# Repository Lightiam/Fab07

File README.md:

# Fab07: ASIC GPU Fab Clean Readiness Package

This repository contains a complete, submission-ready fab clean package for building an ASIC GPU targeting the LightRail AI platform. The materials are organized following industry best practices for ASIC design and fabrication.

## Package Overview

This fab clean readiness package includes:

- **Architecture & Design Documentation** - Complete design specifications and microarchitecture
- **Physical Materials** - Silicon wafer, packaging, and board-level component specifications
- **Logical Materials** - IP blocks, RTL guidelines, and design architecture
- **Design Flow** - Complete toolchain and design methodology
- **Verification & Test** - Comprehensive verification strategy
- **NCE Reference Design** - Ready-to-adapt Neural Calibration Engine for LightRail AI

## Directory Structure

```
fab07/
├── README.md                          # This file
├── docs/                              # Design documentation
│   ├── ARCHITECTURE.md               # Overall system architecture
│   ├── MATERIALS_PHYSICAL.md         # Silicon, packaging, board specs
│   ├── MATERIALS_LOGICAL.md          # IP blocks and RTL guidelines
│   ├── DESIGN_FLOW.md                # Design methodology
│   └── COST_FEASIBILITY.md           # Cost and feasibility analysis
├── specs/                             # Detailed specifications
│   ├── silicon_spec.md               # Silicon wafer and process specs
│   ├── packaging_spec.md             # Package substrate specifications
│   ├── board_spec.md                 # Board-level materials and design
│   ├── thermal_spec.md               # Thermal and mechanical specs
│   └── ip_stack_spec.md              # IP core stack specifications
├── rtl/                               # RTL design and templates
│   ├── core/                         # GPU core modules
│   │   ├── simd_lane.sv              # SIMD execution lanes
│   │   ├── register_file.sv          # Register file architecture
│   │   └── cache_hierarchy.sv        # L0/L1/L2 cache implementation
│   ├── control/                      # Control plane modules
│   │   ├── command_processor.sv      # Host interface controller
│   │   ├── scheduler.sv              # Kernel and stream scheduler
│   │   └── dispatcher.sv             # Event-driven dispatcher
│   ├── memory/                       # Memory subsystem
│   │   ├── memory_controller.sv      # DDR/GDDR interface
│   │   └── l2_cache.sv               # L2/victim cache
│   ├── interfaces/                   # External interface IP
│   │   ├── pcie_controller.sv        # PCIe Gen4/5/6 PHY wrapper
│   │   └── memory_phy.sv             # DDR/LPDR/HBM PHY interface
│   ├── clock_power/                  # Clocking and power
│   │   ├── pll.sv                    # Phase-locked loops
│   │   └── power_gating.sv           # Power domain management
│   ├── test/                         # DFT and test
│   │   ├── scan_chain.sv             # Scan insertion framework
│   │   └── mbist_controller.sv       # SRAM MBIST
│   └── top/                          # Top-level design
│       └── gpu_asic_top.sv           # Top-level GPU module
├── verification/                     # Verification suite
│   ├── testbenches/                  # Unit and system testbenches
│   │   ├── lane_tb.sv                # SIMD lane testbench
│   │   ├── dispatcher_tb.sv          # Dispatcher testbench
│   │   └── system_tb.sv              # Full system testbench
│   ├── tests/                        # Test programs
│   │   ├── smoke_tests.sv            # Basic functionality tests
│   │   ├── regression_tests.sv       # Comprehensive regression suite
│   │   └── performance_tests.sv      # Performance validation
│   ├── uvm/                          # UVM verification framework
│   │   ├── env/                      # Verification environment
│   │   └── sequences/                # Test sequences
│   └── constraints/                  # Design constraints
│       ├── timing.sdc                # Timing constraints
│       └── power.tcl                 # Power constraints
├── tools/                            # Design flow tools and scripts
│   ├── synthesis/                    # Synthesis scripts
│   │   └── dc_synth.tcl              # Design Compiler flow
│   ├── pnr/                          # Place & Route flow
│   │   └── innovus_flow.tcl          # Innovus P&R script
│   ├── simulation/                   # Simulation infrastructure
│   │   ├── verilator_config.cpp      # Verilator configuration
│   │   └── vcs_waves.do              # Waveform capture setup
│   ├── lint/                         # Code quality checks
│   │   ├── verilint.cfg              # Verilint configuration
│   │   └── spyglass.waiver           # SpyGlass waiver file
│   └── dft/                          # DFT generation
│       ├── scan_def.txt              # Scan insertion definition
│       └── mbist_def.txt             # MBIST insertion definition
├── simulation/                       # Pre-built simulation models
│   ├── verilog/                      # RTL simulation models
│   └── spice/                        # SPICE extraction (as applicable)
├── implementation/                   # Physical implementation
│   ├── gds/                          # GDS-II layout files (after P&R)
│   ├── lef/                          # LEF macro definitions
│   ├── lib/                          # Liberty timing/power models
│   └── sdc/                          # Synopsys Design Constraints
├── nce_reference/                    # NCE (Neural Calibration Engine) Reference Design
│   ├── README.md                     # NCE design guide
│   ├── nce_core_top.sv               # Top-level NCE module
│   ├── components/                   # NCE component library
│   │   ├── simd_lane_nce.sv          # 128-lane SIMD datapath
│   │   ├── spiking_dispatcher.sv     # Event-triggered dispatcher
│   │   ├── neuron_block.sv           # 8-neuron calibration block
│   │   └── optical_output.sv         # Differential optical drivers
│   ├── validation/                   # NCE validation suite
│   │   ├── nce_smoke_test.sv         # Basic NCE test
│   │   └── nce_system_test.cpp       # Full NCE validation
│   └── lightrail_adaptation.md       # Guide to adapt NCE for LightRail AI
├── materials/                        # Bill of Materials and sourcing
│   ├── BOM.csv                       # Complete bill of materials
│   ├── SUPPLIERS.md                  # Supplier and vendor contacts
│   ├── IP_LICENSES.md                # IP licensing matrix
│   └── OPEN_SOURCE_STACK.md          # Open-source components used
├── reports/                          # Design reports and analyses
│   ├── ARCHITECTURE_REPORT.md        # Architecture analysis
│   ├── POWER_ANALYSIS.md             # Power estimation and breakdown
│   ├── TIMING_REPORT.md              # Timing closure analysis
│   ├── AREA_REPORT.md                # Area and resource utilization
│   └── COST_BREAKDOWN.md             # Cost analysis and ROI
├── checklists/                       # Pre-submission checklists
│   ├── PRE_SYNTHESIS.md              # Pre-synthesis checklist
│   ├── PRE_PNR.md                    # Pre-P&R checklist
│   ├── PRE_SIGNOFF.md                # Pre-signoff checklist
│   ├── FAB_SUBMISSION.md             # Fab submission checklist
│   └── DFT_VERIFICATION.md           # DFT verification checklist
└── standards/                        # Design standards and guidelines
    ├── CODING_STANDARDS.md           # Verilog coding standards
    ├── DESIGN_PATTERNS.md            # Reusable design patterns
    └── VERIFICATION_METHODOLOGY.md   # Verification methodology
```

## Key Artifacts

### 1. Physical Materials Stack
- **Silicon**: TSMC 28HPC/16FFC or GlobalFoundries 22FDX (mature nodes for cost-effective tapeout)
- **Packaging**: 2-3 layer organic laminate BGA substrate with signal/power planes
- **Board**: FR-4 high-speed PCB with 10-16 layers, optimized for PCIe + DDR4/GDDR6
- **Cooling**: Vapor chamber or copper heatsink with thermal interface materials

### 2. Logical Materials (IP Stack)
- **GPU Core**: 128-lane SIMD with vector ALUs, warp/wavefront scheduler
- **Memory Hierarchy**: L0/L1 per-lane caches, shared L2/L3 with victim buffers
- **On-chip Memory**: Shared memory/scratchpad for thread groups, register files
- **Control Plane**: Command processor, kernel scheduler, firmware management CPU
- **External Interfaces**: PCIe Gen4/5/6 PHY + controller, DDR4/GDDR6/HBM PHY
- **Clocking & Power**: PLL, clock gating, power domains, DVFS support

### 3. Design Flow (Complete Toolchain)
- **Front-end**: SystemVerilog/Verilog, simulation (Verilator/VCS/QuestaSim)
- **Synthesis**: Design Compiler or Genus for RTL-to-gate
- **Place & Route**: Innovus or OpenROAD for physical design
- **Verification**: UVM environment, formal verification, DRC/LVS closure
- **DFT**: Scan chains, MBIST for embedded SRAM, JTAG/boundary scan

### 4. Reference Design: NCE for LightRail AI
A 128-lane neuromorphic computation engine optimized for sparse spike-based ML inference:
- **Architecture**: Event-driven spiking dispatcher with watchdog-based clock gating
- **Datapath**: 128-lane SIMD with bfloat16 precision, vector registers
- **Calibration Block**: 8-neuron SPI-controlled neuron calibration with DAC/comparator interface
- **Optical I/O**: Modulated differential optical outputs for direct spike transmission
- **Memory**: Shared SRAM for synaptic weights, SPI-based external configuration

## Getting Started

### 1. Review Architecture
Start with `docs/ARCHITECTURE.md` for the overall system design and rationale.

### 2. Examine Specifications
Review the detailed specifications in `specs/` directory:
- Silicon and process technology choices
- Package substrate design
- PCB board specifications
- IP core stack and interface specifications

### 3. Explore RTL Design
The `rtl/` directory contains modular, synthesizable Verilog/SystemVerilog:
- Each core module is self-contained with clear I/O contracts
- Design follows GPU best practices from VeriGPU and OpenGPU
- Register file and memory interfaces use parametrized templates

### 4. Run Verification
See `verification/README.md` for:
- Simulation setup and execution
- Testbench architecture
- Coverage metrics and closure

### 5. Adapt NCE for LightRail
Follow `nce_reference/lightrail_adaptation.md` to customize the Neural Calibration Engine for your specific LightRail AI workloads.

## Dependencies and Open-Source Stack

This design builds on proven open-source components:

| Component | Source | Purpose |
|-----------|--------|---------|
| GPU Core RTL | VeriGPU | ML-focused RISC-V GPU architecture |
| Alt. GPU Ref | OpenGPU, MIAOW | Graphics pipeline, microarchitecture inspiration |
| ASIC Flow | VLSI-ASIC-Design-Flow | Full RTL-to-GDS open flow |
| ASIC Tools | ZeroASIC projects | Lambdapdk, SiliconCompiler, Switchboard |
| Memory IP | Foundry PDK | Embedded SRAM macros, I/O libraries |
| External IP | Licensed | PCIe PHY, DDR PHY controllers |

## Design Methodology

### Complexity Reduction Strategy
- **Narrow workload focus**: Transformer inference + 8-bit matmul tensor operations
- **Simple starting point**: One or two GPU clusters, no display output
- **Cost optimization**: Mature node (28nm/22nm) instead of cutting-edge

### NRE Budget (Realistic Estimates)
- **High NRE**: $5-8M for complete ASIC tapeout (engineering, EDA, masks)
- **Mid-range**: $2-4M for focused "GPU-like" accelerator
- **Breakeven**: ~22k units at $45/unit BOM cost for custom ASIC ROI

### Timeline
- **Phase 1** (2-3 months): RTL design, verification, and synthesis closure
- **Phase 2** (2-3 months): Place & Route, timing/power closure, DFT insertion
- **Phase 3** (1-2 months): Physical verification, mask generation, tapeout
- **Phase 4** (6-9 months): Wafer fab, packaging, validation

## Submission Checklist

Before fab submission, verify:

- [ ] All RTL passes lint and static analysis
- [ ] Synthesis achieves timing closure at target speed
- [ ] P&R meets all timing, power, and area targets
- [ ] DFT insertion complete with scan test coverage >95%
- [ ] DRC/LVS clean with zero violations
- [ ] Power budget validated via static and dynamic analysis
- [ ] Thermal analysis confirms safe operating margins
- [ ] IO signal integrity verified (SSN, crosstalk)
- [ ] Mask data preparation (OASIS) complete
- [ ] Final design review and signoff documentation

## Production Materials & Specifications

### LightRail AI Platform Documentation
- **docs/LIGHTRAIL_GEN3_ASIC_FAB_SPEC.pdf** - Complete Gen3 ASIC tapeout specification with electrical, thermal, and interface requirements
- **docs/VRM_BRINGUP_GUIDE.md** - 24-phase DrMOS power delivery and voltage regulator bring-up protocol with unpowered and powered verification procedures

### NCE Reference Implementation
- **nce_reference/** - Complete Neural Calibration Engine (NCE) design package including:
  - RTL for 128-lane SIMD MAC with BF16→Q8.8 fixed-point conversion
  - TFLN (Thin-Film Lithium Niobate) optical driver interface
  - Hardware Abstraction Layer (C HAL) for register access and calibration
  - PCB design materials (BOM, routing guides, characteristics)

## References and Resources

### ASIC Design Guides
- AnyASilicon's "Ridiculously Smart Guide to Developing Your Own ASIC"
- Perplexity's comprehensive ASIC GPU materials guide (this repo's source document)
- LightRail Gen3 ASIC Fab Specification (see docs/)

### Open-Source GPU Projects
- **VeriGPU** (GitHub): ML-focused GPU in Verilog, RISC-V based, ASIC tape-out target
- **OpenGPU** (GitHub): Graphics-focused GPU, VHDL implementation
- **MIAOW** (GitHub): Open GPGPU microarchitecture and implementation

### ASIC Flow and Tools
- **VLSI-ASIC-Design-Flow**: Complete open-source RTL-to-GDS flow
- **ZeroASIC Projects**:
  - Lambdapdk: Standardized PDK collection
  - SiliconCompiler: Build system for silicon
  - Switchboard: Hardware communication framework

### Educational Resources
- TinyTapeout: Shuttle service for small custom ASIC projects
- ChipTalk community for design reviews and feedback

## Contributing

This is a submission-ready design package. For modifications:

1. Update relevant documentation in `docs/` and `specs/`
2. Make RTL changes in `rtl/` with full verification
3. Update verification suite in `verification/`
4. Run complete regression and DFT verification
5. Update relevant checklists

## License

See LICENSE file for details. This design package uses a mix of open-source and licensed components—refer to `materials/IP_LICENSES.md` for detailed IP licensing matrix.

---

**Last Updated**: July 2026
**Status**: Fab Clean - Ready for Submission
**Target Process**: TSMC 28HPC / GlobalFoundries 22FDX

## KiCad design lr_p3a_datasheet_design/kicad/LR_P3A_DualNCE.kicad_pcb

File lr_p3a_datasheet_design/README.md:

# 15 — LR-P3A Rev 6.3 Authoritative Datasheet Design

This folder ingests the owner-supplied **LightRail AI Gen3 NCE Datasheet Rev 3.0**
(`LightRail_Gen3_NCE_Datasheet_Rev3.0.pdf`, "Production Release for Seeed Studio
Fusion PCBA") as the **authoritative electrical design source** — the thing the
repo had been missing.

Start here: `DATASHEET_RECONCILIATION_AND_BUILD_PLAN.md`.

## Why this matters

The datasheet describes a **real, buildable board (LR-P3A Rev 6.3)** with
complete real data — and it is **a different board than the repo's
`TFLN_AI_NODE_X2`**. Critically, it places the NCE ASIC + HBM stacks **inside the
co-packaged (CPO) module on a silicon interposer**, so the board-level
NCE/HBM ball-map blocker that gated `09`/`10` **does not apply** to this design.

## Authoritative data captured (`data/`)

| File | Datasheet source |
| --- | --- |
| `bom_table9.csv` | Table 9 — full BOM, real MPNs |
| `pinout_U1_modulator.csv` | Table 5 — NTT/iXblue TFLN-MZM-400G-C (17 pins) |
| `pinout_U2_laser.csv` | Table 6 — NeoPhotonics TLN-1550-100 (8 pins) |
| `pinout_U3_photodetector.csv` | Table 7 — Finisar XPDV4120R (4 pins) |
| `pinout_U4_hmc8410.csv` | Table 8 — ADI HMC8410 (8 pins) |
| `stackup_15L_table2.csv` | Table 2 — 15-layer Rogers/FR-4 hybrid |
| `netclasses_table3.csv` | Table 3 — impedance/width/gap per net class |
| `lr_p3a_netlist_v1.csv` | Built from §9 power tree + §1.3/§6 signal chain + connector tables |

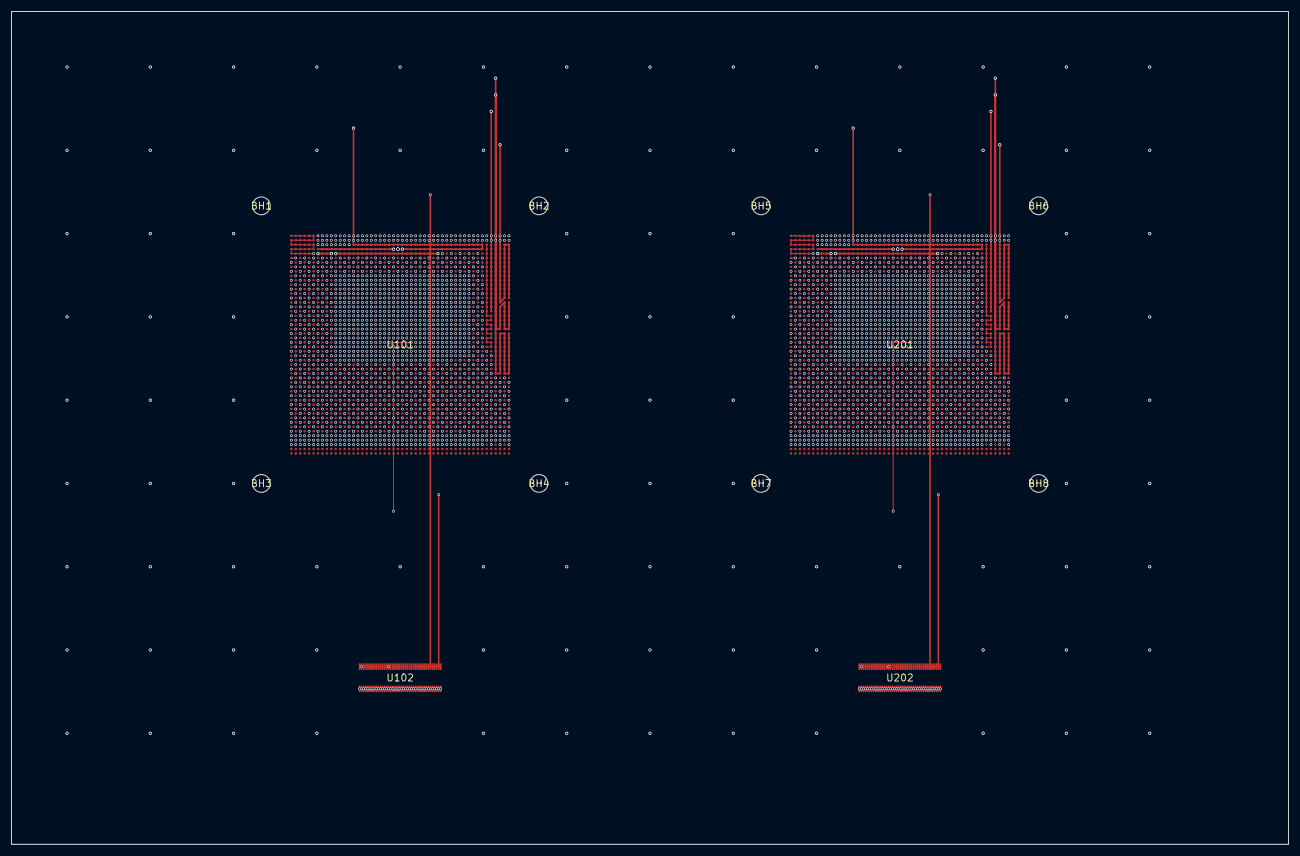
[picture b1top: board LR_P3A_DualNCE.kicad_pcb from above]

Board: 16 copper layers, 230.0 x 150.0 mm, 12 parts (0 on the bottom side), 26 nets.

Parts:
BH1, BH2, BH3, BH4, BH5, BH6, BH7, BH8: (no value)
U101, U201: BGA-2500_40x40_P0.8mm_NCE
U102, U202: TFLN-MZM-400G-C

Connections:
+0V9: U102.35, U102.36, U102.37, U102.38, U202.35, U202.36, U202.37, U202.38
+3V3: U102.39, U102.40, U202.39, U202.40
BIAS_TUNE_A: U102.17, U102.18, U102.19, U102.20, U102.21, U102.22, U102.23, U102.24
BIAS_TUNE_B: U202.17, U202.18, U202.19, U202.20, U202.21, U202.22, U202.23, U202.24
GND: U101.AA1, U101.AA3, U101.AA5, U101.AA7, U101.AA9, U101.AA43, U101.AB2, U101.AB4, U101.AB6, U101.AB8, U101.AB10, U101.AB42, U101.AB44, U101.AC1, U101.AC3, U101.AC5, U101.AC7, U101.AC9, U101.AC43, U101.AD2, U101.AD4, U101.AD6, U101.AD8, U101.AD10, U101.AD42, U101.AD44, U101.AE1, U101.AE3, U101.AE5, U101.AE7, U101.AE9, U101.AE43, U101.AF2, U101.AF4, U101.AF6, U101.AF8, U101.AF10, U101.AF42, U101.AF44, U101.AG1, U101.AG3, U101.AG5, U101.AG7, U101.AG9, U101.AG43, U101.AG45, U101.AH2, U101.AH4, U101.AH6, U101.AH8, U101.AH10, U101.AH42, U101.AH44, U101.AH46, U101.AJ1, U101.AJ3, U101.AJ5, U101.AJ7, U101.AJ9, U101.AJ39, U101.AJ41, U101.AJ43, U101.AJ45, U101.AK2, U101.AK4, U101.AK6, U101.AK8, U101.AK10, U101.AK12, U101.AK14, U101.AK16, U101.AK18, U101.AK20, U101.AK22, U101.AK24, U101.AK26, U101.AK28, U101.AK30, U101.AK32, U101.AK34, U101.AK36, U101.AK38, U101.AK40, U101.AK42, U101.AK44, U101.AK46, U101.AL1, U101.AL3, U101.AL5, U101.AL7, U101.AL9, U101.AL11, U101.AL13, U101.AL15, U101.AL17, U101.AL19, U101.AL21, U101.AL23, U101.AL25, U101.AL27, U101.AL29, U101.AL31, U101.AL33, U101.AL35, U101.AL37, U101.AL39, U101.AL41, U101.AL43, U101.AL45, U101.AM2, U101.AM4, U101.AM6, U101.AM8, U101.AM10, U101.AM12, U101.AM14, U101.AM16, U101.AM18, U101.AM20, U101.AM22, U101.AM24, U101.AM26, U101.AM28, U101.AM30, U101.AM32, U101.AM34, U101.AM36, U101.AM38, U101.AM40, U101.AM42, U101.AM44, U101.AM46, U101.AN1, U101.AN3, U101.AN5, U101.AN7, U101.AN9, U101.AN11, U101.AN13, U101.AN15, U101.AN17, U101.AN19, U101.AN21, U101.AN23, U101.AN25, U101.AN27, U101.AN29, U101.AN31, U101.AN33, U101.AN35, U101.AN37, U101.AN39, U101.AN41, U101.AN43, U101.AN45, U101.AN47, U101.AN49, U101.AP2, U101.AP4, U101.AP6, U101.AP8, U101.AP10, U101.AP12, U101.AP14, U101.AP16, U101.AP18, U101.AP20, U101.AP22, U101.AP24, U101.AP26, U101.AP28, U101.AP30, U101.AP32, U101.AP34, U101.AP36, U101.AP38, U101.AP40, U101.AP42, U101.AP44, U101.AP46, U101.AP48, U101.AP50, U101.AR1, U101.AR3, U101.AR5, U101.AR7, U101.AR9, U101.AR11, U101.AR13, U101.AR15, U101.AR17, U101.AR19, U101.AR21, U101.AR23, U101.AR25, U101.AR27, U101.AR29, U101.AR31, U101.AR33, U101.AR35, U101.AR37, U101.AR39, U101.AR41, U101.AR43, U101.AR45, U101.AR47, U101.AR49, U101.AT2, U101.AT4, U101.AT6, U101.AT8, U101.AT10, U101.AT12, U101.AT14, U101.AT16, U101.AT18, U101.AT20, U101.AT22, U101.AT24, U101.AT26, U101.AT28, U101.AT30, U101.AT32, U101.AT34, U101.AT36, U101.AT38, U101.AT40, U101.AT42, U101.AT44, U101.AT46, U101.AT48, U101.AT50, U101.AU1, U101.AU3, U101.AU5, U101.AU7, U101.AU9, U101.AU11, U101.AU13, U101.AU15, U101.AU17, U101.AU19, U101.AU21, U101.AU23, U101.AU25, U101.AU27, U101.AU29, U101.AU31, U101.AU33, U101.AU35, U101.AU37, U101.AU39, U101.AU41, U101.AU43, U101.AU45, U101.AU47, U101.AU49, U101.AV2, U101.AV4, U101.AV6, U101.AV8, U101.AV10, U101.AV12, U101.AV14, U101.AV16, U101.AV18, U101.AV20, U101.AV22, U101.AV24, U101.AV26, U101.AV28, U101.AV30, U101.AV32, U101.AV34, U101.AV36, U101.AV38, U101.AV40, U101.AV42, U101.AV44, U101.AV46, U101.AV48, U101.AV50, U101.AW1, U101.AW3, U101.AW5, U101.AW7, U101.AW9, U101.AW11, U101.AW13, U101.AW15, U101.AW17, U101.AW19, U101.AW21, U101.AW23, U101.AW25, U101.AW27, U101.AW29, U101.AW31, U101.AW33, U101.AW35, U101.AW37, U101.AW39, U101.AW41, U101.AW43, U101.AW45, U101.AW47, U101.AW49, U101.AY2, U101.AY4, U101.AY6, U101.AY8, U101.AY10, U101.AY12, U101.AY14, U101.AY16, U101.AY18, U101.AY20, U101.AY22, U101.AY24, U101.AY26, U101.AY28, U101.AY30, U101.AY32, U101.AY34, U101.AY36, U101.AY38, U101.AY40, U101.AY42, U101.AY44, U101.AY46, U101.AY48, U101.AY50, U101.BA1, U101.BA3, U101.BA5, U101.BA7, U101.BA9, U101.BA11, U101.BA13, U101.BA15, U101.BA17, U101.BA19, U101.BA21, U101.BA23, U101.BA25, U101.BA27, U101.BA29, U101.BA31, U101.BA33, U101.BA35, U101.BA37, U101.BA39, U101.BA41, U101.BA43, U101.BA45, U101.BA47, U101.BA49, U101.BB2, U101.BB4, U101.BB6, U101.BB8, U101.BB10, U101.BB12, U101.BB14, U101.BB16, U101.BB18, U101.BB20, U101.BB22, U101.BB24, U101.BB26, U101.BB28, U101.BB30, U101.BB32, U101.BB34, U101.BB36, U101.BB38, U101.BB40, U101.BB42, U101.BB44, U101.BB46, U101.BB48, U101.BB50, U101.BC1, U101.BC3, U101.BC5, U101.BC7, U101.BC9, U101.BC11, U101.BC13, U101.BC15, U101.BC17, U101.BC19, U101.BC21, U101.BC23, U101.BC25, U101.BC27, U101.BC29, U101.BC31, U101.BC33, U101.BC35, U101.BC37, U101.BC39, U101.BC41, U101.BC43, U101.BC45, U101.BC47, U101.BC49, U101.BD2, U101.BD4, U101.BD6, U101.BD8, U101.BD10, U101.BD12, U101.BD14, U101.BD16, U101.BD18, U101.BD20, U101.BD22, U101.BD24, U101.BD26, U101.BD28, U101.BD30, U101.BD32, U101.BD34, U101.BD36, U101.BD38, U101.BD40, U101.BD42, U101.BD44, U101.BD46, U101.BD48, U101.BD50, U101.BE1, U101.BE3, U101.BE5, U101.BE7, U101.BE9, U101.BE11, U101.BE13, U101.BE15, U101.BE17, U101.BE19, U101.BE21, U101.BE23, U101.BE25, U101.BE27, U101.BE29, U101.BE31, U101.BE33, U101.BE35, U101.BE37, U101.BE39, U101.BE41, U101.BE43, U101.BE45, U101.BE47, U101.BE49, U101.BH46, U101.BH48, U101.BH50, U101.E35, U101.E37, U101.E39, U101.E41, U101.E43, U101.F4, U101.F6, U101.F8, U101.F10, U101.F12, U101.F14, U101.F16, U101.F18, U101.F20, U101.F22, U101.F24, U101.F26, U101.F28, U101.F30, U101.F32, U101.F34, U101.F36, U101.F38, U101.F40, U101.F42, U101.F44, U101.G1, U101.G3, U101.G5, U101.G7, U101.G9, U101.G11, U101.G13, U101.G15, U101.G17, U101.G19, U101.G21, U101.G23, U101.G25, U101.G27, U101.G29, U101.G31, U101.G33, U101.G35, U101.G37, U101.G39, U101.G41, U101.G43, U101.H2, U101.H4, U101.H6, U101.H8, U101.H10, U101.H12, U101.H14, U101.H16, U101.H18, U101.H20, U101.H22, U101.H24, U101.H26, U101.H28, U101.H30, U101.H32, U101.H34, U101.H36, U101.H38, U101.H40, U101.H42, U101.H44, U101.J1, U101.J3, U101.J5, U101.J7, U101.J9, U101.J11, U101.J13, U101.J15, U101.J17, U101.J19, U101.J21, U101.J23, U101.J25, U101.J27, U101.J29, U101.J31, U101.J33, U101.J35, U101.J37, U101.J39, U101.J41, U101.J43, U101.K2, U101.K4, U101.K6, U101.K8, U101.K10, U101.K42, U101.K44, U101.L1, U101.L3, U101.L5, U101.L7, U101.L9, U101.L43, U101.M2, U101.M4, U101.M6, U101.M8, U101.M10, U101.M42, U101.M44, U101.N1, U101.N3, U101.N5, U101.N7, U101.N9, U101.N43, U101.P2, U101.P4, U101.P6, U101.P8, U101.P10, U101.P42, U101.P44, U101.R1, U101.R3, U101.R5, U101.R7, U101.R9, U101.R43, U101.T2, U101.T4, U101.T6, U101.T8, U101.T10, U101.T42, U101.T44, U101.U1, U101.U3, U101.U5, U101.U7, U101.U9, U101.U43, U101.V2, U101.V4, U101.V6, U101.V8, U101.V10, U101.V42, U101.V44, U101.W1, U101.W3, U101.W5, U101.W7, U101.W9, U101.W43, U101.Y2, U101.Y4, U101.Y6, U101.Y8, U101.Y10, U101.Y42, U101.Y44, U102.41, U102.42, U102.43, U102.44, U102.45, U102.46, U102.47, U102.48, U102.49, U102.50, U102.51, U102.52, U102.53, U102.54, U102.55, U102.56, U102.57, U102.58, U102.59, U102.60, U102.61, U102.62, U102.63, U102.64, U102.65, U102.66, U102.67, U102.68, U102.69, U102.70, U102.71, U102.72, U102.73, U102.74, U102.75, U102.76, U102.77, U102.78, U102.79, U102.80, U201.AA1, U201.AA3, U201.AA5, U201.AA7, U201.AA9, U201.AA43, U201.AB2, U201.AB4, U201.AB6, U201.AB8, U201.AB10, U201.AB42, U201.AB44, U201.AC1, U201.AC3, U201.AC5, U201.AC7, U201.AC9, U201.AC43, U201.AD2, U201.AD4, U201.AD6, U201.AD8, U201.AD10, U201.AD42, U201.AD44, U201.AE1, U201.AE3, U201.AE5, U201.AE7, U201.AE9, U201.AE43, U201.AF2, U201.AF4, U201.AF6, U201.AF8, U201.AF10, U201.AF42, U201.AF44, U201.AG1, U201.AG3, U201.AG5, U201.AG7, U201.AG9, U201.AG43, U201.AG45, U201.AH2, U201.AH4, U201.AH6, U201.AH8, U201.AH10, U201.AH42, U201.AH44, U201.AH46, U201.AJ1, U201.AJ3, U201.AJ5, U201.AJ7, U201.AJ9, U201.AJ39, U201.AJ41, U201.AJ43, U201.AJ45, U201.AK2, U201.AK4, U201.AK6, U201.AK8, U201.AK10, U201.AK12, U201.AK14, U201.AK16, U201.AK18, U201.AK20, U201.AK22, U201.AK24, U201.AK26, U201.AK28, U201.AK30, U201.AK32, U201.AK34, U201.AK36, U201.AK38, U201.AK40, U201.AK42, U201.AK44, U201.AK46, U201.AL1, U201.AL3, U201.AL5, U201.AL7, U201.AL9, U201.AL11, U201.AL13, U201.AL15, U201.AL17, U201.AL19, U201.AL21, U201.AL23, U201.AL25, U201.AL27, U201.AL29, U201.AL31, U201.AL33, U201.AL35, U201.AL37, U201.AL39, U201.AL41, U201.AL43, U201.AL45, U201.AM2, U201.AM4, U201.AM6, U201.AM8, U201.AM10, U201.AM12, U201.AM14, U201.AM16, U201.AM18, U201.AM20, U201.AM22, U201.AM24, U201.AM26, U201.AM28, U201.AM30, U201.AM32, U201.AM34, U201.AM36, U201.AM38, U201.AM40, U201.AM42, U201.AM44, U201.AM46, U201.AN1, U201.AN3, U201.AN5, U201.AN7, U201.AN9, U201.AN11, U201.AN13, U201.AN15, U201.AN17, U201.AN19, U201.AN21, U201.AN23, U201.AN25, U201.AN27, U201.AN29, U201.AN31, U201.AN33, U201.AN35, U201.AN37, U201.AN39, U201.AN41, U201.AN43, U201.AN45, U201.AN47, U201.AN49, U201.AP2, U201.AP4, U201.AP6, U201.AP8, U201.AP10, U201.AP12, U201.AP14, U201.AP16, U201.AP18, U201.AP20, U201.AP22, U201.AP24, U201.AP26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
HBM4_SIDECH_A: U101.AA45, U101.AA46, U101.AB45, U101.AB46, U101.AC45, U101.AC46, U101.AD45, U101.AD46, U101.AE45, U101.AE46, U101.AF45, U101.AF46, U101.C45, U101.D45, U101.E45, U101.F45, U101.G45, U101.H45, U101.J45, U101.K45, U101.L45, U101.M45, U101.N45, U101.P45, U101.R45, U101.T45, U101.U45, U101.V45, U101.W45, U101.W46, U101.Y45, U101.Y46
HBM4_SIDECH_B: U201.AA45, U201.AA46, U201.AB45, U201.AB46, U201.AC45, U201.AC46, U201.AD45, U201.AD46, U201.AE45, U201.AE46, U201.AF45, U201.AF46, U201.C45, U201.D45, U201.E45, U201.F45, U201.G45, U201.H45, U201.J45, U201.K45, U201.L45, U201.M45, U201.N45, U201.P45, U201.R45, U201.T45, U201.U45, U201.V45, U201.W45, U201.W46, U201.Y45, U201.Y46
HBM4_VDDC: U101.C48, U101.C49, U101.C50, U101.D48, U101.D49, U101.D50, U101.E48, U101.E49, U101.E50, U101.F48, U101.F49, U101.F50, U101.G48, U101.G49, U101.G50, U101.H48, U101.H49, U101.H50, U101.J48, U101.J49, U101.J50, U101.K48, U101.K49, U101.K50, U101.L48, U101.L49, U101.L50, U101.M48, U101.M49, U101.M50, U101.N48, U101.N49, U101.N50, U101.P48, U101.P49, U101.P50, U101.R48, U101.R49, U101.R50, U101.T48, U201.C48, U201.C49, U201.C50, U201.D48, U201.D49, U201.D50, U201.E48, U201.E49, U201.E50, U201.F48, U201.F49, U201.F50, U201.G48, U201.G49, U201.G50, U201.H48, U201.H49, U201.H50, U201.J48, U201.J49, U201.J50, U201.K48, U201.K49, U201.K50, U201.L48, U201.L49, U201.L50, U201.M48, U201.M49, U201.M50, U201.N48, U201.N49, U201.N50, U201.P48, U201.P49, U201.P50, U201.R48, U201.R49, U201.R50, U201.T48
HBM4_VDDQ: U101.AC47, U101.AC48, U101.AC49, U101.AC50, U101.AD47, U101.AD48, U101.AD49, U101.AD50, U101.AE47, U101.AE48, U101.AE49, U101.AE50, U101.AF47, U101.AF48, U101.AF49, U101.AF50, U101.AG47, U101.AG48, U101.AG49, U101.AG50, U101.AH47, U101.AH48, U101.AH49, U101.AH50, U101.AJ47, U101.AJ48, U101.AJ49, U101.AJ50, U101.AK47, U101.AK48, U101.AK49, U101.AK50, U101.AL47, U101.AL48, U101.AL49, U101.AL50, U101.AM47, U101.AM48, U101.AM49, U101.AM50, U201.AC47, U201.AC48, U201.AC49, U201.AC50, U201.AD47, U201.AD48, U201.AD49, U201.AD50, U201.AE47, U201.AE48, U201.AE49, U201.AE50, U201.AF47, U201.AF48, U201.AF49, U201.AF50, U201.AG47, U201.AG48, U201.AG49, U201.AG50, U201.AH47, U201.AH48, U201.AH49, U201.AH50, U201.AJ47, U201.AJ48, U201.AJ49, U201.AJ50, U201.AK47, U201.AK48, U201.AK49, U201.AK50, U201.AL47, U201.AL48, U201.AL49, U201.AL50, U201.AM47, U201.AM48, U201.AM49, U201.AM50
HBM4_VDDQL: U101.AA47, U101.AA48, U101.AA49, U101.AA50, U101.AB47, U101.AB48, U101.AB49, U101.AB50, U101.C47, U101.D47, U101.E47, U101.F47, U101.G47, U101.H47, U101.J47, U101.K47, U101.L47, U101.M47, U101.N47, U101.P47, U101.R47, U101.T47, U101.T49, U101.T50, U101.U47, U101.U48, U101.U49, U101.U50, U101.V47, U101.V48, U101.V49, U101.V50, U101.W47, U101.W48, U101.W49, U101.W50, U101.Y47, U101.Y48, U101.Y49, U101.Y50, U201.AA47, U201.AA48, U201.AA49, U201.AA50, U201.AB47, U201.AB48, U201.AB49, U201.AB50, U201.C47, U201.D47, U201.E47, U201.F47, U201.G47, U201.H47, U201.J47, U201.K47, U201.L47, U201.M47, U201.N47, U201.P47, U201.R47, U201.T47, U201.T49, U201.T50, U201.U47, U201.U48, U201.U49, U201.U50, U201.V47, U201.V48, U201.V49, U201.V50, U201.W47, U201.W48, U201.W49, U201.W50, U201.Y47, U201.Y48, U201.Y49, U201.Y50
HBM4_VPP: U101.C46, U101.D46, U101.E46, U101.F46, U101.G46, U101.H46, U101.J46, U101.K46, U101.L46, U101.M46, U101.N46, U101.P46, U101.R46, U101.T46, U101.U46, U101.V46, U201.C46, U201.D46, U201.E46, U201.F46, U201.G46, U201.H46, U201.J46, U201.K46, U201.L46, U201.M46, U201.N46, U201.P46, U201.R46, U201.T46, U201.U46, U201.V46
MGMT_A: U101.A1, U101.A2, U101.A3, U101.A4, U101.A5, U101.A6, U101.B1, U101.B2, U101.B3, U101.B4, U101.B5, U101.B6, U101.C1, U101.C2, U101.C3, U101.C4, U101.C5, U101.C6, U101.D1, U101.D2, U101.D3, U101.D4, U101.D5, U101.D6, U101.E1, U101.E2, U101.E3, U101.E4, U101.E5, U101.E6, U101.F1, U101.F2
MGMT_B: U201.A1, U201.A2, U201.A3, U201.A4, U201.A5, U201.A6, U201.B1, U201.B2, U201.B3, U201.B4, U201.B5, U201.B6, U201.C1, U201.C2, U201.C3, U201.C4, U201.C5, U201.C6, U201.D1, U201.D2, U201.D3, U201.D4, U201.D5, U201.D6, U201.E1, U201.E2, U201.E3, U201.E4, U201.E5, U201.E6, U201.F1, U201.F2
PCIE_G6_A: U101.BF1, U101.BF2, U101.BF3, U101.BF4, U101.BF5, U101.BF6, U101.BF7, U101.BF8, U101.BF9, U101.BF10, U101.BF11, U101.BF12, U101.BF13, U101.BF14, U101.BF15, U101.BF16, U101.BF17, U101.BF18, U101.BF19, U101.BF20, U101.BF21, U101.BF22, U101.BF23, U101.BF24, U101.BF25, U101.BF26, U101.BF27, U101.BF28, U101.BF29, U101.BF30, U101.BF31, U101.BF32, U101.BF33, U101.BF34, U101.BF35, U101.BF36, U101.BF37, U101.BF38, U101.BF39, U101.BF40, U101.BF41, U101.BF42, U101.BF43, U101.BF44, U101.BF45, U101.BF46, U101.BF47, U101.BF48, U101.BF49, U101.BF50, U101.BG1, U101.BG2, U101.BG3, U101.BG4, U101.BG5, U101.BG6, U101.BG7, U101.BG8, U101.BG9, U101.BG10, U101.BG11, U101.BG12, U101.BG13, U101.BG14, U101.BG15, U101.BG16, U101.BG17, U101.BG18, U101.BG19, U101.BG20, U101.BG21, U101.BG22, U101.BG23, U101.BG24, U101.BG25, U101.BG26, U101.BG27, U101.BG28, U101.BG29, U101.BG30, U101.BG31, U101.BG32, U101.BG33, U101.BG34, U101.BG35, U101.BG36, U101.BG37, U101.BG38, U101.BG39, U101.BG40, U101.BG41, U101.BG42, U101.BG43, U101.BG44, U101.BG45, U101.BG46, U101.BG47, U101.BG48, U101.BG49, U101.BG50, U101.BH1, U101.BH2, U101.BH3, U101.BH4, U101.BH5, U101.BH6, U101.BH7, U101.BH8, U101.BH9, U101.BH10, U101.BH11, U101.BH12, U101.BH13, U101.BH14, U101.BH15, U101.BH16, U101.BH17, U101.BH18, U101.BH19, U101.BH20, U101.BH21, U101.BH22, U101.BH23, U101.BH24, U101.BH25, U101.BH26, U101.BH27, U101.BH28, U101.BH29, U101.BH30, U101.BH31, U101.BH32, U101.BH33, U101.BH34, U101.BH35, U101.BH36, U101.BH37, U101.BH38, U101.BH39, U101.BH40, U101.BH41, U101.BH42, U101.BH43, U101.BH44
PCIE_G6_B: U201.BF1, U201.BF2, U201.BF3, U201.BF4, U201.BF5, U201.BF6, U201.BF7, U201.BF8, U201.BF9, U201.BF10, U201.BF11, U201.BF12, U201.BF13, U201.BF14, U201.BF15, U201.BF16, U201.BF17, U201.BF18, U201.BF19, U201.BF20, U201.BF21, U201.BF22, U201.BF23, U201.BF24, U201.BF25, U201.BF26, U201.BF27, U201.BF28, U201.BF29, U201.BF30, U201.BF31, U201.BF32, U201.BF33, U201.BF34, U201.BF35, U201.BF36, U201.BF37, U201.BF38, U201.BF39, U201.BF40, U201.BF41, U201.BF42, U201.BF43, U201.BF44, U201.BF45, U201.BF46, U201.BF47, U201.BF48, U201.BF49, U201.BF50, U201.BG1, U201.BG2, U201.BG3, U201.BG4, U201.BG5, U201.BG6, U201.BG7, U201.BG8, U201.BG9, U201.BG10, U201.BG11, U201.BG12, U201.BG13, U201.BG14, U201.BG15, U201.BG16, U201.BG17, U201.BG18, U201.BG19, U201.BG20, U201.BG21, U201.BG22, U201.BG23, U201.BG24, U201.BG25, U201.BG26, U201.BG27, U201.BG28, U201.BG29, U201.BG30, U201.BG31, U201.BG32, U201.BG33, U201.BG34, U201.BG35, U201.BG36, U201.BG37, U201.BG38, U201.BG39, U201.BG40, U201.BG41, U201.BG42, U201.BG43, U201.BG44, U201.BG45, U201.BG46, U201.BG47, U201.BG48, U201.BG49, U201.BG50, U201.BH1, U201.BH2, U201.BH3, U201.BH4, U201.BH5, U201.BH6, U201.BH7, U201.BH8, U201.BH9, U201.BH10, U201.BH11, U201.BH12, U201.BH13, U201.BH14, U201.BH15, U201.BH16, U201.BH17, U201.BH18, U201.BH19, U201.BH20, U201.BH21, U201.BH22, U201.BH23, U201.BH24, U201.BH25, U201.BH26, U201.BH27, U201.BH28, U201.BH29, U201.BH30, U201.BH31, U201.BH32, U201.BH33, U201.BH34, U201.BH35, U201.BH36, U201.BH37, U201.BH38, U201.BH39, U201.BH40, U201.BH41, U201.BH42, U201.BH43, U201.BH44
PD_MON_A: U102.27, U102.28, U102.29, U102.30, U102.31, U102.32, U102.33, U102.34
PD_MON_B: U202.27, U202.28, U202.29, U202.30, U202.31, U202.32, U202.33, U202.34
PWR_CORE: U101.AA11, U101.AA12, U101.AA13, U101.AA14, U101.AA15, U101.AA16, U101.AA17, U101.AA18, U101.AA19, U101.AA20, U101.AA21, U101.AA22, U101.AA23, U101.AA24, U101.AA25, U101.AA26, U101.AA27, U101.AA28, U101.AA29, U101.AA30, U101.AA31, U101.AA32, U101.AA33, U101.AA34, U101.AA35, U101.AA36, U101.AA37, U101.AA38, U101.AA39, U101.AA40, U101.AA41, U101.AB11, U101.AB12, U101.AB13, U101.AB14, U101.AB15, U101.AB16, U101.AB17, U101.AB18, U101.AB19, U101.AB20, U101.AB21, U101.AB22, U101.AB23, U101.AB24, U101.AB25, U101.AB26, U101.AB27, U101.AB28, U101.AB29, U101.AB30, U101.AB31, U101.AB32, U101.AB33, U101.AB34, U101.AB35, U101.AB36, U101.AB37, U101.AB38, U101.AB39, U101.AB40, U101.AB41, U101.AC11, U101.AC12, U101.AC13, U101.AC14, U101.AC15, U101.AC16, U101.AC17, U101.AC18, U101.AC19, U101.AC20, U101.AC21, U101.AC22, U101.AC23, U101.AC24, U101.AC25, U101.AC26, U101.AC27, U101.AC28, U101.AC29, U101.AC30, U101.AC31, U101.AC32, U101.AC33, U101.AC34, U101.AC35, U101.AC36, U101.AC37, U101.AC38, U101.AC39, U101.AC40, U101.AC41, U101.AD11, U101.AD12, U101.AD13, U101.AD14, U101.AD15, U101.AD16, U101.AD17, U101.AD18, U101.AD19, U101.AD20, U101.AD21, U101.AD22, U101.AD23, U101.AD24, U101.AD25, U101.AD26, U101.AD27, U101.AD28, U101.AD29, U101.AD30, U101.AD31, U101.AD32, U101.AD33, U101.AD34, U101.AD35, U101.AD36, U101.AD37, U101.AD38, U101.AD39, U101.AD40, U101.AD41, U101.AE11, U101.AE12, U101.AE13, U101.AE14, U101.AE15, U101.AE16, U101.AE17, U101.AE18, U101.AE19, U101.AE20, U101.AE21, U101.AE22, U101.AE23, U101.AE28, U101.AE29, U101.AE30, U101.AE31, U101.AE32, U101.AE33, U101.AE34, U101.AE35, U101.AE36, U101.AE37, U101.AE38, U101.AE39, U101.AE40, U101.AE41, U101.AF11, U101.AF12, U101.AF13, U101.AF14, U101.AF15, U101.AF16, U101.AF17, U101.AF18, U101.AF19, U101.AF20, U101.AF21, U101.AF22, U101.AF23, U101.AF24, U101.AF25, U101.AF26, U101.AF27, U101.AF28, U101.AF29, U101.AF30, U101.AF31, U101.AF32, U101.AF33, U101.AF34, U101.AF35, U101.AF36, U101.AF37, U101.AF38, U101.AF39, U101.AF40, U101.AF41, U101.AG11, U101.AG12, U101.AG13, U101.AG14, U101.AG15, U101.AG16, U101.AG17, U101.AG18, U101.AG19, U101.AG20, U101.AG21, U101.AG22, U101.AG23, U101.AG24, U101.AG25, U101.AG26, U101.AG27, U101.AG28, U101.AG29, U101.AG30, U101.AG31, U101.AG32, U101.AG33, U101.AG34, U101.AG35, U101.AG36, U101.AG37, U101.AG38, U101.AG39, U101.AG40, U101.AG41, U101.AH11, U101.AH12, U101.AH13, U101.AH14, U101.AH15, U101.AH16, U101.AH17, U101.AH18, U101.AH19, U101.AH20, U101.AH21, U101.AH22, U101.AH23, U101.AH24, U101.AH25, U101.AH26, U101.AH27, U101.AH28, U101.AH29, U101.AH30, U101.AH31, U101.AH32, U101.AH33, U101.AH34, U101.AH35, U101.AH36, U101.AH37, U101.AH38, U101.AH39, U101.AH40, U101.AH41, U101.AJ11, U101.AJ12, U101.AJ13, U101.AJ14, U101.AJ15, U101.AJ16, U101.AJ17, U101.AJ18, U101.AJ19, U101.AJ20, U101.AJ21, U101.AJ22, U101.AJ23, U101.AJ24, U101.AJ25, U101.AJ26, U101.AJ27, U101.AJ28, U101.AJ29, U101.AJ30, U101.AJ31, U101.AJ32, U101.AJ33, U101.AJ34, U101.AJ35, U101.AJ36, U101.AJ37, U101.K11, U101.K12, U101.K13, U101.K14, U101.K15, U101.K16, U101.K17, U101.K18, U101.K19, U101.K20, U101.K21, U101.K22, U101.K23, U101.K24, U101.K25, U101.K26, U101.K27, U101.K28, U101.K29, U101.K30, U101.K31, U101.K32, U101.K33, U101.K34, U101.K35, U101.K36, U101.K37, U101.K38, U101.K39, U101.K40, U101.K41, U101.L11, U101.L12, U101.L13, U101.L14, U101.L15, U101.L16, U101.L17, U101.L18, U101.L19, U101.L20, U101.L21, U101.L22, U101.L23, U101.L24, U101.L25, U101.L26, U101.L27, U101.L28, U101.L29, U101.L30, U101.L31, U101.L32, U101.L33, U101.L34, U101.L35, U101.L36, U101.L37, U101.L38, U101.L39, U101.L40, U101.L41, U101.M11, U101.M12, U101.M13, U101.M14, U101.M15, U101.M16, U101.M17, U101.M18, U101.M19, U101.M20, U101.M21, U101.M22, U101.M23, U101.M24, U101.M25, U101.M26, U101.M27, U101.M28, U101.M29, U101.M30, U101.M31, U101.M32, U101.M33, U101.M34, U101.M35, U101.M36, U101.M37, U101.M38, U101.M39, U101.M40, U101.M41, U101.N11, U101.N12, U101.N13, U101.N14, U101.N15, U101.N16, U101.N17, U101.N18, U101.N19, U101.N20, U101.N21, U101.N22, U101.N23, U101.N24, U101.N25, U101.N26, U101.N27, U101.N28, U101.N29, U101.N30, U101.N31, U101.N32, U101.N33, U101.N34, U101.N35, U101.N36, U101.N37, U101.N38, U101.N39, U101.N40, U101.N41, U101.P11, U101.P12, U101.P13, U101.P14, U101.P15, U101.P16, U101.P17, U101.P18, U101.P19, U101.P20, U101.P21, U101.P22, U101.P23, U101.P24, U101.P25, U101.P26, U101.P27, U101.P28, U101.P29, U101.P30, U101.P31, U101.P32, U101.P33, U101.P34, U101.P35, U101.P36, U101.P37, U101.P38, U101.P39, U101.P40, U101.P41, U101.R11, U101.R12, U101.R13, U101.R14, U101.R15, U101.R16, U101.R17, U101.R18, U101.R19, U101.R20, U101.R21, U101.R22, U101.R23, U101.R24, U101.R25, U101.R26, U101.R27, U101.R28, U101.R29, U101.R30, U101.R31, U101.R32, U101.R33, U101.R34, U101.R35, U101.R36, U101.R37, U101.R38, U101.R39, U101.R40, U101.R41, U101.T11, U101.T12, U101.T13, U101.T14, U101.T15, U101.T16, U101.T17, U101.T18, U101.T19, U101.T20, U101.T21, U101.T22, U101.T23, U101.T24, U101.T25, U101.T26, U101.T27, U101.T28, U101.T29, U101.T30, U101.T31, U101.T32, U101.T33, U101.T34, U101.T35, U101.T36, U101.T37, U101.T38, U101.T39, U101.T40, U101.T41, U101.U11, U101.U12, U101.U13, U101.U14, U101.U15, U101.U16, U101.U17, U101.U18, U101.U19, U101.U20, U101.U21, U101.U22, U101.U23, U101.U24, U101.U25, U101.U26, U101.U27, U101.U28, U101.U29, U101.U30, U101.U31, U101.U32, U101.U33, U101.U34, U101.U35, U101.U36, U101.U37, U101.U38, U101.U39, U101.U40, U101.U41, U101.V11, U101.V12, U101.V13, U101.V14, U101.V15, U101.V16, U101.V17, U101.V18, U101.V19, U101.V20, U101.V21, U101.V22, U101.V23, U101.V24, U101.V25, U101.V26, U101.V27, U101.V28, U101.V29, U101.V30, U101.V31, U101.V32, U101.V33, U101.V34, U101.V35, U101.V36, U101.V37, U101.V38, U101.V39, U101.V40, U101.V41, U101.W11, U101.W12, U101.W13, U101.W14, U101.W15, U101.W16, U101.W17, U101.W18, U101.W19, U101.W20, U101.W21, U101.W22, U101.W23, U101.W24, U101.W25, U101.W26, U101.W27, U101.W28, U101.W29, U101.W30, U101.W31, U101.W32, U101.W33, U101.W34, U101.W35, U101.W36, U101.W37, U101.W38, U101.W39, U101.W40, U101.W41, U101.Y11, U101.Y12, U101.Y13, U101.Y14, U101.Y15, U101.Y16, U101.Y17, U101.Y18, U101.Y19, U101.Y20, U101.Y21, U101.Y22, U101.Y23, U101.Y24, U101.Y25, U101.Y26, U101.Y27, U101.Y28, U101.Y29, U101.Y30, U101.Y31, U101.Y32, U101.Y33, U101.Y34, U101.Y35, U101.Y36, U101.Y37, U101.Y38, U101.Y39, U101.Y40, U101.Y41, U201.AA11, U201.AA12, U201.AA13, U201.AA14, U201.AA15, U201.AA16, U201.AA17, U201.AA18, U201.AA19, U201.AA20, U201.AA21, U201.AA22, U201.AA23, U201.AA24, U201.AA25, U201.AA26, U201.AA27, U201.AA28, U201.AA29, U201.AA30, U201.AA31, U201.AA32, U201.AA33, U201.AA34, U201.AA35, U201.AA36, U201.AA37, U201.AA38, U201.AA39, U201.AA40, U201.AA41, U201.AB11, U201.AB12, U201.AB13, U201.AB14, U201.AB15, U201.AB16, U201.AB17, U201.AB18, U201.AB19, U201.AB20, U201.AB21, U201.AB22, U201.AB23, U201.AB24, U201.AB25, U201.AB26, U201.AB27, U201.AB28, U201.AB29, U201.AB30, U201.AB31, U201.AB32, U201.AB33, U201.AB34, U201.AB35, U201.AB36, U201.AB37, U201.AB38, U201.AB39, U201.AB40, U201.AB41, U201.AC11, U201.AC12, U201.AC13, U201.AC14, U201.AC15, U201.AC16, U201.AC17, U201.AC18, U201.AC19, U201.AC20, U201.AC21, U201.AC22, U201.AC23, U201.AC24, U201.AC25, U201.AC26, U201.AC27, U201.AC28, U201.AC29, U201.AC30, U201.AC31, U201.AC32, U201.AC33, U201.AC34, U201.AC35, U201.AC36, U201.AC37, U201.AC38, U201.AC39, U201.AC40, U201.AC41, U201.AD11, U201.AD12, U201.AD13, U201.AD14, U201.AD15, U201.AD16, U201.AD17, U201.AD18, U201.AD19, U201.AD20, U201.AD21, U201.AD22, U201.AD23, U201.AD24, U201.AD25, U201.AD26, U201.AD27, U201.AD28, U201.AD29, U201.AD30, U201.AD31, U201.AD32, U201.AD33, U201.AD34, U201.AD35, U201.AD36, U201.AD37, U201.AD38, U201.AD39, U201.AD40, U201.AD41, U201.AE11, U201.AE12, U201.AE13, U201.AE14, U201.AE15, U201.AE16, U201.AE17, U201.AE18, U201.AE19, U201.AE20, U201.AE21, U201.AE22, U201.AE23, U201.AE28, U201.AE29, U201.AE30, U201.AE31, U201.AE32, U201.AE33, U201.AE34, U201.AE35, U201.AE36, U201.AE37, U201.AE38, U201.AE39, U201.AE40, U201.AE41, U201.AF11, U201.AF12, U201.AF13, U201.AF14, U201.AF15, U201.AF16, U201.AF17, U201.AF18, U201.AF19, U201.AF20, U201.AF21, U201.AF22, U201.AF23, U201.AF24, U201.AF25, U201.AF26, U201.AF27, U201.AF28, U201.AF29, U201.AF30, U201.AF31, U201.AF32, U201.AF33, U201.AF34, U201.AF35, U201.AF36, U201.AF37, U201.AF38, U201.AF39, U201.AF40, U201.AF41, U201.AG11, U201.AG12, U201.AG13, U201.AG14, U201.AG15, U201.AG16, U201.AG17, U201.AG18, U201.AG19, U201.AG20, U201.AG21, U201.AG22, U201.AG23, U201.AG24, U201.AG25, U201.AG26, U201.AG27, U201.AG28, U201.AG29, U201.AG30, U201.AG31, U201.AG32, U201.AG33, U201.AG34, U201.AG35, U201.AG36, U201.AG37, U201.AG38, U201.AG39, U201.AG40, U201.AG41, U201.AH11, U201.AH12, U201.AH13, U201.AH14, U201.AH15, U201.AH16, U201.AH17, U201.AH18, U201.AH19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
SERDES_200G_A: U101.A7, U101.A8, U101.A9, U101.A10, U101.A11, U101.A12, U101.A13, U101.A14, U101.A15, U101.A16, U101.A17, U101.A18, U101.A19, U101.A20, U101.A21, U101.A22, U101.A23, U101.A24, U101.A25, U101.A26, U101.A27, U101.A28, U101.A29, U101.A30, U101.A31, U101.A32, U101.A33, U101.A34, U101.A35, U101.A36, U101.A37, U101.A38, U101.A39, U101.A40, U101.A41, U101.A42, U101.A43, U101.A44, U101.A45, U101.A46, U101.A47, U101.A48, U101.A49, U101.A50, U101.B7, U101.B8, U101.B9, U101.B10, U101.B11, U101.B12, U101.B13, U101.B14, U101.B15, U101.B16, U101.B17, U101.B18, U101.B19, U101.B20, U101.B21, U101.B22, U101.B23, U101.B24, U101.B25, U101.B26, U101.B27, U101.B28, U101.B29, U101.B30, U101.B31, U101.B32, U101.B33, U101.B34, U101.B35, U101.B36, U101.B37, U101.B38, U101.B39, U101.B40, U101.B41, U101.B42, U101.B43, U101.B44, U101.B45, U101.B46, U101.B47, U101.B48, U101.B49, U101.B50, U101.C7, U101.C8, U101.C9, U101.C10, U101.C11, U101.C12, U101.C13, U101.C14
SERDES_200G_B: U201.A7, U201.A8, U201.A9, U201.A10, U201.A11, U201.A12, U201.A13, U201.A14, U201.A15, U201.A16, U201.A17, U201.A18, U201.A19, U201.A20, U201.A21, U201.A22, U201.A23, U201.A24, U201.A25, U201.A26, U201.A27, U201.A28, U201.A29, U201.A30, U201.A31, U201.A32, U201.A33, U201.A34, U201.A35, U201.A36, U201.A37, U201.A38, U201.A39, U201.A40, U201.A41, U201.A42, U201.A43, U201.A44, U201.A45, U201.A46, U201.A47, U201.A48, U201.A49, U201.A50, U201.B7, U201.B8, U201.B9, U201.B10, U201.B11, U201.B12, U201.B13, U201.B14, U201.B15, U201.B16, U201.B17, U201.B18, U201.B19, U201.B20, U201.B21, U201.B22, U201.B23, U201.B24, U201.B25, U201.B26, U201.B27, U201.B28, U201.B29, U201.B30, U201.B31, U201.B32, U201.B33, U201.B34, U201.B35, U201.B36, U201.B37, U201.B38, U201.B39, U201.B40, U201.B41, U201.B42, U201.B43, U201.B44, U201.B45, U201.B46, U201.B47, U201.B48, U201.B49, U201.B50, U201.C7, U201.C8, U201.C9, U201.C10, U201.C11, U201.C12, U201.C13, U201.C14
TEC_TH_A: U102.25, U102.26
TEC_TH_B: U202.25, U202.26
TFLN_RF_A: U102.1, U102.2, U102.3, U102.4, U102.5, U102.6, U102.7, U102.8, U102.9, U102.10, U102.11, U102.12, U102.13, U102.14, U102.15, U102.16
TFLN_RF_B: U202.1, U202.2, U202.3, U202.4, U202.5, U202.6, U202.7, U202.8, U202.9, U202.10, U202.11, U202.12, U202.13, U202.14, U202.15, U202.16
THERMAL: U101.AE24, U101.AE25, U101.AE26, U101.AE27, U201.AE24, U201.AE25, U201.AE26, U201.AE27
VDD_IO: U101.C15, U101.C16, U101.C17, U101.C18, U101.C19, U101.C20, U101.C21, U101.C22, U101.C23, U101.C24, U101.C25, U101.C26, U101.C27, U101.C28, U101.C29, U101.C30, U101.C31, U101.C32, U101.C33, U101.C34, U101.C35, U101.C36, U101.C37, U101.C38, U101.C39, U101.C40, U101.C41, U101.C42, U101.C43, U101.C44, U101.D7, U101.D8, U101.D9, U101.D10, U101.D11, U101.D12, U101.D13, U101.D14, U101.D15, U101.D16, U101.D17, U101.D18, U101.D19, U101.D20, U101.D21, U101.D22, U101.D23, U101.D24, U101.D25, U101.D26, U101.D27, U101.D28, U101.D29, U101.D30, U101.D31, U101.D32, U101.D33, U101.D34, U101.D35, U101.D36, U101.D37, U101.D38, U101.D39, U101.D40, U101.D41, U101.D42, U101.D43, U101.D44, U101.E7, U101.E8, U101.E9, U101.E10, U101.E11, U101.E12, U101.E13, U101.E14, U101.E15, U101.E16, U101.E17, U101.E18, U101.E19, U101.E20, U101.E21, U101.E22, U101.E23, U101.E24, U101.E25, U101.E26, U101.E27, U101.E28, U101.E29, U101.E30, U101.E31, U101.E32, U101.E33, U101.E34, U201.C15, U201.C16, U201.C17, U201.C18, U201.C19, U201.C20, U201.C21, U201.C22, U201.C23, U201.C24, U201.C25, U201.C26, U201.C27, U201.C28, U201.C29, U201.C30, U201.C31, U201.C32, U201.C33, U201.C34, U201.C35, U201.C36, U201.C37, U201.C38, U201.C39, U201.C40, U201.C41, U201.C42, U201.C43, U201.C44, U201.D7, U201.D8, U201.D9, U201.D10, U201.D11, U201.D12, U201.D13, U201.D14, U201.D15, U201.D16, U201.D17, U201.D18, U201.D19, U201.D20, U201.D21, U201.D22, U201.D23, U201.D24, U201.D25, U201.D26, U201.D27, U201.D28, U201.D29, U201.D30, U201.D31, U201.D32, U201.D33, U201.D34, U201.D35, U201.D36, U201.D37, U201.D38, U201.D39, U201.D40, U201.D41, U201.D42, U201.D43, U201.D44, U201.E7, U201.E8, U201.E9, U201.E10, U201.E11, U201.E12, U201.E13, U201.E14, U201.E15, U201.E16, U201.E17, U201.E18, U201.E19, U201.E20, U201.E21, U201.E22, U201.E23, U201.E24, U201.E25, U201.E26, U201.E27, U201.E28, U201.E29, U201.E30, U201.E31, U201.E32, U201.E33, U201.E34

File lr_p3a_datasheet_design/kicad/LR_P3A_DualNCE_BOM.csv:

Refs,Value,Footprint,Qty,DNP
"BH1, BH2, BH3, BH4, BH5, BH6, BH7, BH8",,,8,
"U101, U201",,BGA-2500_40x40_P0.8mm_NCE,2,
"U102, U202",TFLN-MZM-400G-C,,2,

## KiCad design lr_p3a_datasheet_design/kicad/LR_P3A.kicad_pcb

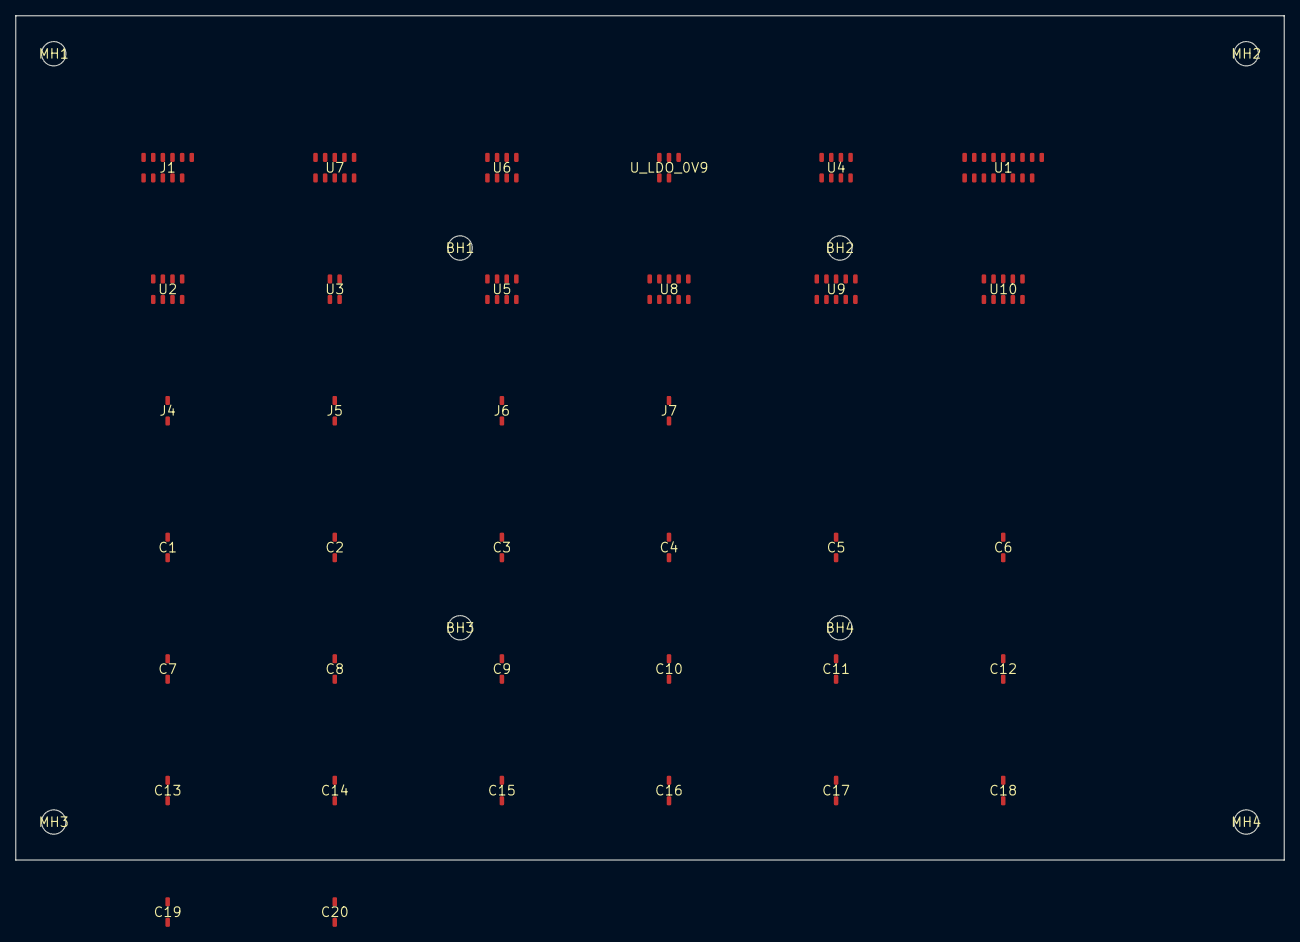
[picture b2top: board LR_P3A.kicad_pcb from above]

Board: 16 copper layers, 167.0 x 111.2 mm, 44 parts (0 on the bottom side), 10 nets, no tracks yet.

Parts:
BH1, BH2, BH3, BH4: (no value)
C1: C1
C2: C2
C3: C3
C4: C4
C5: C5
C6: C6
C7: C7
C8: C8
C9: C9
C10: C10
C11: C11
C12: C12
C13: C13
C14: C14
C15: C15
C16: C16
C17: C17
C18: C18
C19: C19
C20: C20
J1: J1
J4: J4
J5: J5
J6: J6
J7: J7
MH1, MH2, MH3, MH4: (no value)
U1: U1
U2: U2
U3: U3
U4: U4
U5: U5
U6: U6
U7: U7
U8: U8
U9: U9
U10: U10
U_LDO_0V9: U_LDO_0V9

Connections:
+0V9: C17.1, C18.1, U1.10
+1V8: C13.1, C14.1, C15.1, C16.1
+2V5_LASER: C19.1, C20.1, U2.1
+3V3: C5.1, C6.1, C7.1, C8.1, C9.1, C10.1, C11.1, C12.1, U1.9, U4.5
+12V_IN: C1.1, C2.1, C3.1, C4.1
BIAS_TUNE_0: J6.1, U1.7
BIAS_TUNE_1: J7.1, U1.8
GND: C1.2, C2.2, C3.2, C4.2, C5.2, C6.2, C7.2, C8.2, C9.2, C10.2, C11.2, C12.2, C13.2, C14.2, C15.2, C16.2, C17.2, C18.2, C19.2, C20.2, J4.2, J5.2, J6.2, J7.2, U1.3, U1.6, U1.14, U1.17, U2.2, U2.4, U2.6, U3.4, U4.8
TFLN_DRV_N: J5.1, U1.2, U1.5, U4.4
TFLN_DRV_P: J4.1, U1.1, U1.4, U4.3
